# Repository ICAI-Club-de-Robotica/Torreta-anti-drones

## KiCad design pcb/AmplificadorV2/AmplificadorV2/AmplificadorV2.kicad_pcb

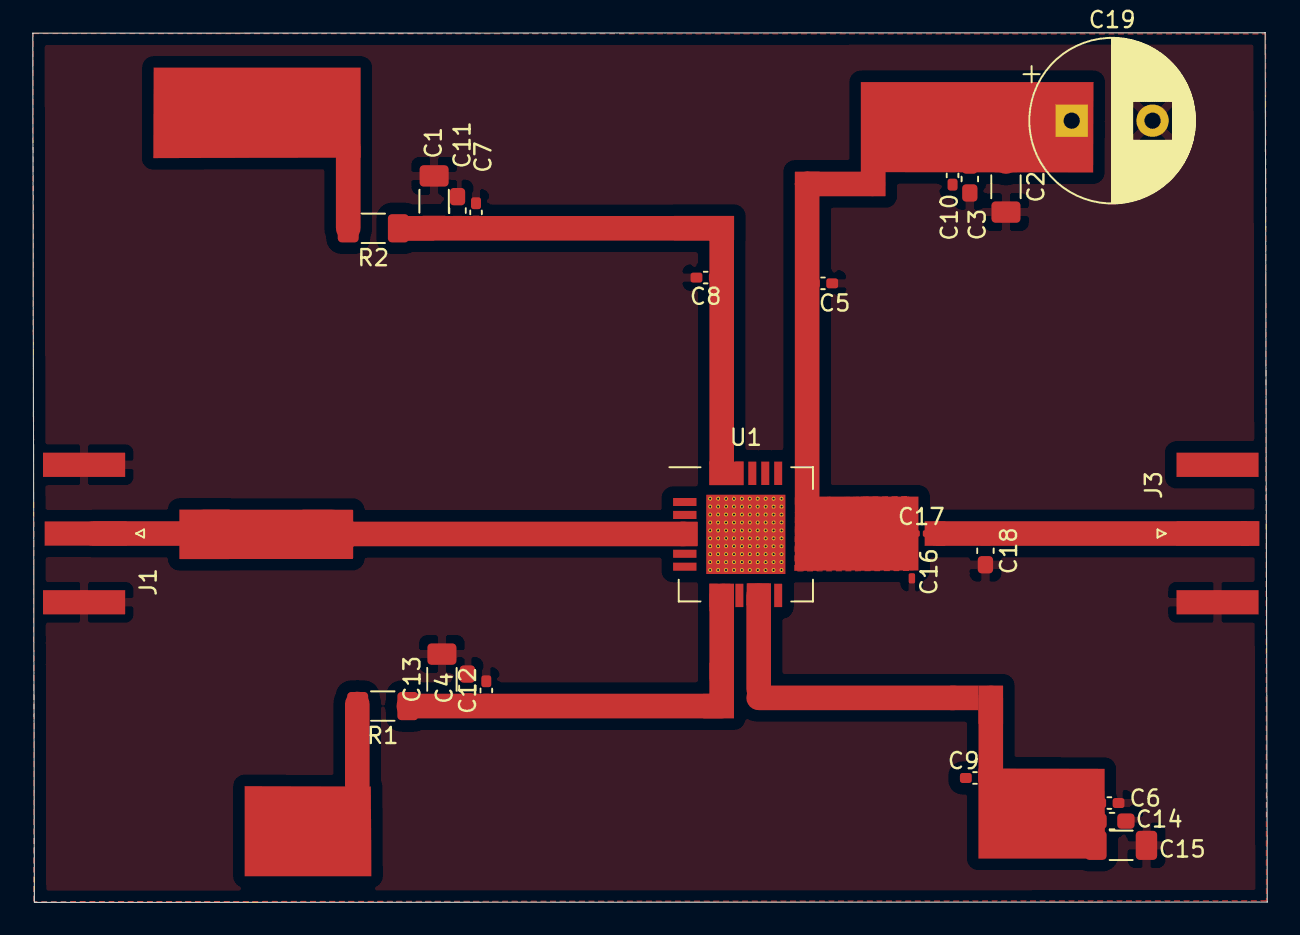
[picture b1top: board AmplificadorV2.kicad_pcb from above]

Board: 4 copper layers, 76.3 x 53.8 mm, 24 parts (0 on the bottom side), 7 nets.

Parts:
C1, C2, C13, C15: 10uF; C_1206_3216Metric_Pad1.33x1.80mm_HandSolder
C3, C4, C11, C14: 0.1uF; C_0603_1608Metric_Pad1.08x0.95mm_HandSolder
C5, C6, C7, C8, C9, C10, C12: 5.6pF; C_0402_1005Metric_Pad0.74x0.62mm_HandSolder
C16: 1.6pF; C_0201_0603Metric_Pad0.64x0.40mm_HandSolder
C17: 4.7pF; C_0201_0603Metric_Pad0.64x0.40mm_HandSolder
C18: 0.5pF; C_0603_1608Metric_Pad1.08x0.95mm_HandSolder
C19: 220uF; CP_Radial_D10.0mm_P5.00mm
J1, J3: Conn_01x01_Female; SMA_Amphenol_132289_EdgeMount
R1: 4.7K; R_1206_3216Metric_Pad1.30x1.75mm_HandSolder
R2: 4.7k; R_1206_3216Metric_Pad1.30x1.75mm_HandSolder
U1: MHT2012N; QFN-24_EP_8x8_Pitch0.8mm

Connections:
GND: C1.2, C2.2, C3.2, C4.2, C5.1, C6.2, C7.2, C8.2, C10.2, C11.2, C12.2, C13.2, C14.2, C15.2, C16.2, C18.2, C19.2, J1.2, J3.2
unnamed: C1.1, C4.1, C6.1, R1.1, U1.8
unnamed: C2.1, C3.1, C7.1, C19.1, R2.1, U1.24
unnamed: C12.1, C14.1, C15.1
Rfin: J1.1, U1.3, U1.4
Rfout: C17.1, C18.1, J3.1
outAmpli: C8.1, C9.1, C9.2, C10.1, C11.1, C13.1, C16.1, U1.10, U1.11

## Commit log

2022-01-15 new ampli in progress
2022-02-06 ampli terminado
2022-02-11 avances
2022-02-21 New Data set
2022-02-21 Added new Dataset
2022-02-21 deteccion yolov5
